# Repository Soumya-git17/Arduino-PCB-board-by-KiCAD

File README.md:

# Arduino-PCB-board-by-KiCAD
This repository contains the design files for a custom Arduino-compatible board created using KiCad.

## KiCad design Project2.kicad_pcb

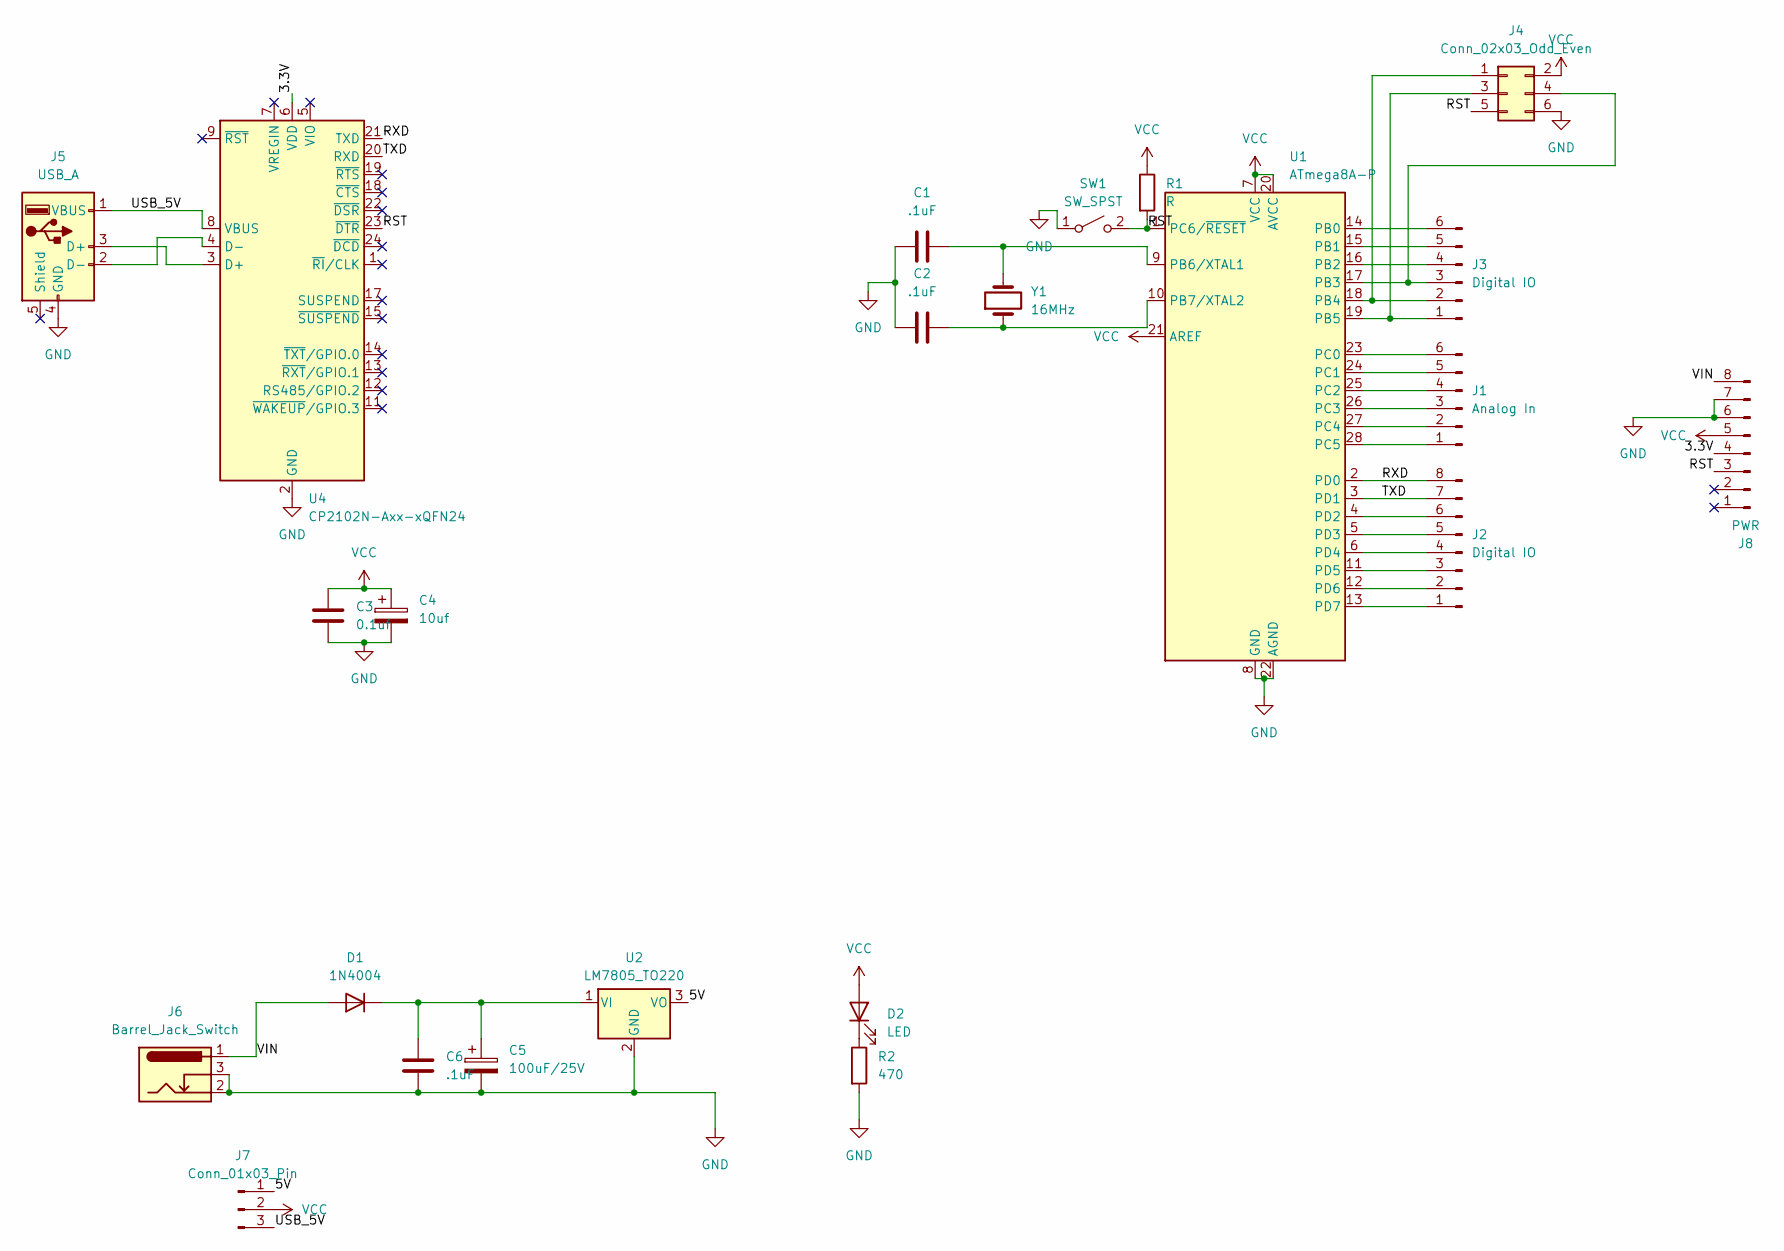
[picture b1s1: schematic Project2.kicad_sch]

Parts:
C1, C2, C6: .1uF; CP_EIA-3216-10_Kemet-I
C3: 0.1uf; CP_EIA-3216-10_Kemet-I
C4: 10uf; CP_Elec_6.3x5.9
C5: 100uF/25V; CP_Elec_6.3x5.9
D1: 1N4004; D_DO-41_SOD81_P10.16mm_Horizontal
D2: LED; LED_1206_3216Metric
J1: Analog In; PinSocket_1x06_P2.54mm_Vertical
J2: Digital IO; PinSocket_1x08_P2.54mm_Vertical
J3: Digital IO; PinSocket_1x06_P2.54mm_Vertical
J4: Conn_02x03_Odd_Even; PinHeader_2x03_P2.54mm_Vertical
J5: USB_A; USB_B_Amphenol_MUSB-D511_Vertical_Rugged
J6: Barrel_Jack_Switch; BarrelJack_CUI_PJ-063AH_Horizontal
J7: Conn_01x03_Pin; PinHeader_2x03_P2.54mm_Vertical
J8: PWR; PinHeader_1x08_P2.54mm_Vertical
R1: R; R_1206_3216Metric
R2: 470; R_1206_3216Metric
SW1: SW_SPST; SW_PUSH_6mm
U1: ATmega8A-P; DIP-28_W7.62mm
U2: LM7805_TO220; TO-220-3_Vertical
U4: CP2102N-Axx-xQFN24; QFN-24-1EP_4x4mm_P0.5mm_EP2.6x2.6mm
Y1: 16MHz; Crystal_HC49-U_Vertical

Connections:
/3.3V: J8.4, U4.6 (VDD)
/5V: J7.1, U2.3 (VO)
/RST: J4.5, J8.3, R1.2, SW1.2 (B), U1.1 (PC6/~RESET), U4.23 (~DTR)
/RXD: J2.8, U1.2 (PD0), U4.21 (TXD)
/TXD: J2.7, U1.3 (PD1), U4.20 (RXD)
/USB_5V: J5.1 (VBUS), J7.3, U4.8 (VBUS)
/VIN: D1.2 (A), J6.1, J8.8
GND: C1.1, C2.1, C3.2, C4.2, C5.2, C6.2, J4.6, J5.4 (GND), J6.2, J6.3, J8.6, J8.7, R2.2, SW1.1 (A), U1.8 (GND), U1.22 (AGND), U2.2 (GND), U4.2 (GND), U4.25 (GND)
unnamed: C5.1, C6.1, D1.1 (K), U2.1 (VI)
unnamed: D2.1 (K), R2.1
unnamed: J1.1, U1.28 (PC5)
unnamed: J1.2, U1.27 (PC4)
unnamed: J1.3, U1.26 (PC3)
unnamed: J1.4, U1.25 (PC2)
unnamed: J1.5, U1.24 (PC1)
unnamed: J1.6, U1.23 (PC0)
unnamed: J2.1, U1.13 (PD7)
unnamed: J2.2, U1.12 (PD6)
unnamed: J2.3, U1.11 (PD5)
unnamed: J2.4, U1.6 (PD4)
unnamed: J2.5, U1.5 (PD3)
unnamed: J2.6, U1.4 (PD2)
unnamed: J3.1, J4.3, U1.19 (PB5)
unnamed: J3.2, J4.1, U1.18 (PB4)
unnamed: J3.3, J4.4, U1.17 (PB3)
unnamed: J3.4, U1.16 (PB2)
unnamed: J3.5, U1.15 (PB1)
unnamed: J3.6, U1.14 (PB0)
unnamed: J5.3 (D+), U4.3 (D+)
unnamed: J5.2 (D-), U4.4 (D-)
unnamed: C1.2, U1.9 (PB6/XTAL1), Y1.2
unnamed: C2.2, U1.10 (PB7/XTAL2), Y1.1
VCC: C3.1, C4.1, D2.2 (A), J4.2, J7.2, J8.5, R1.1, U1.7 (VCC), U1.20 (AVCC), U1.21 (AREF)

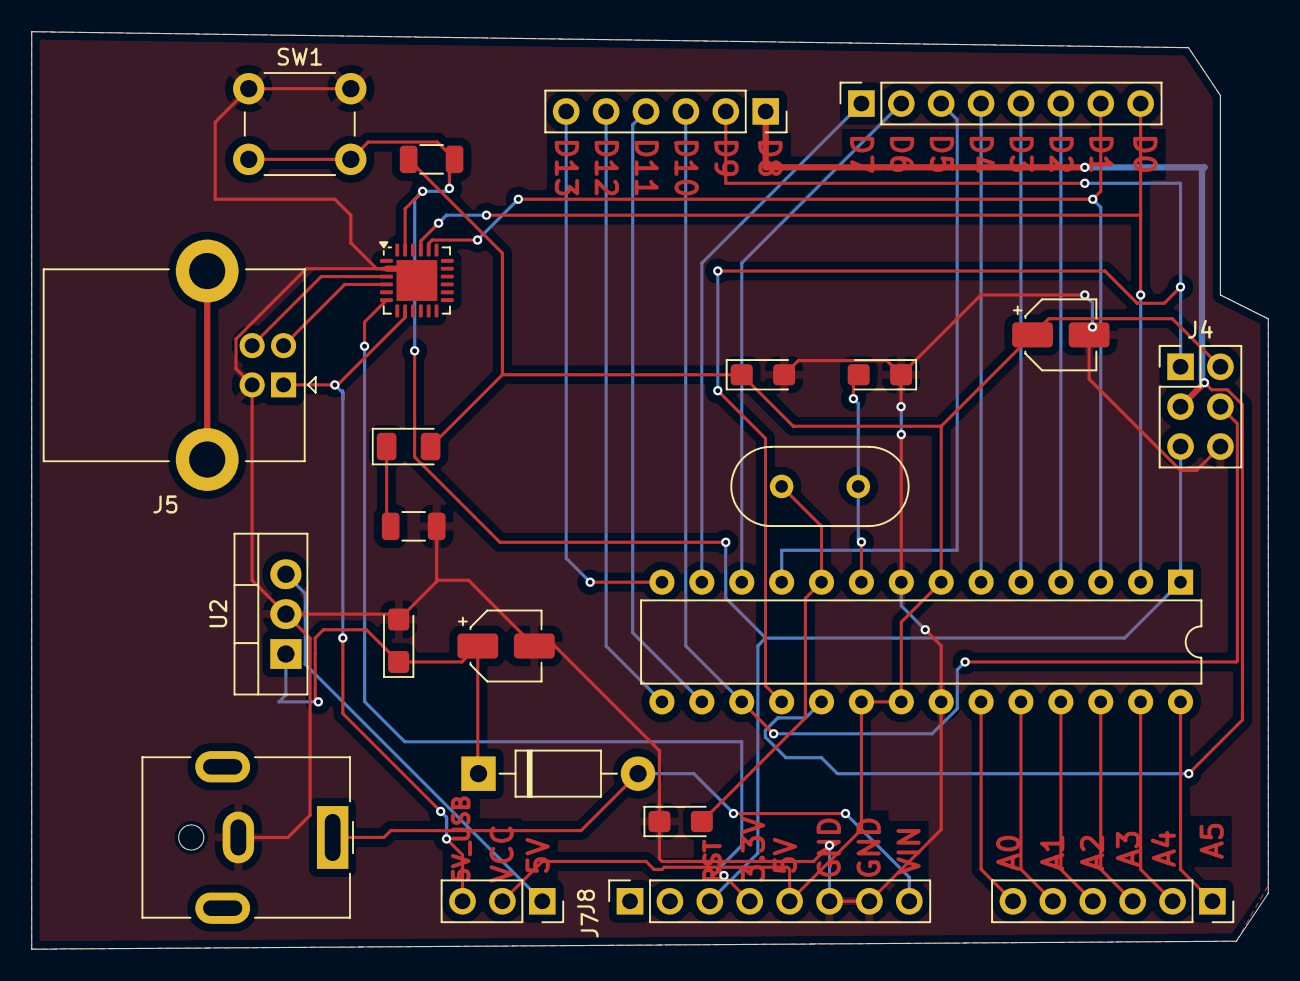
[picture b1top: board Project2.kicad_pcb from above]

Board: 4 copper layers, 78.7 x 58.4 mm, 23 parts (0 on the bottom side), 33 nets.

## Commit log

2025-02-21 Add files via upload
    This repository contains the design files for a custom Arduino-compatible board created using KiCad.
